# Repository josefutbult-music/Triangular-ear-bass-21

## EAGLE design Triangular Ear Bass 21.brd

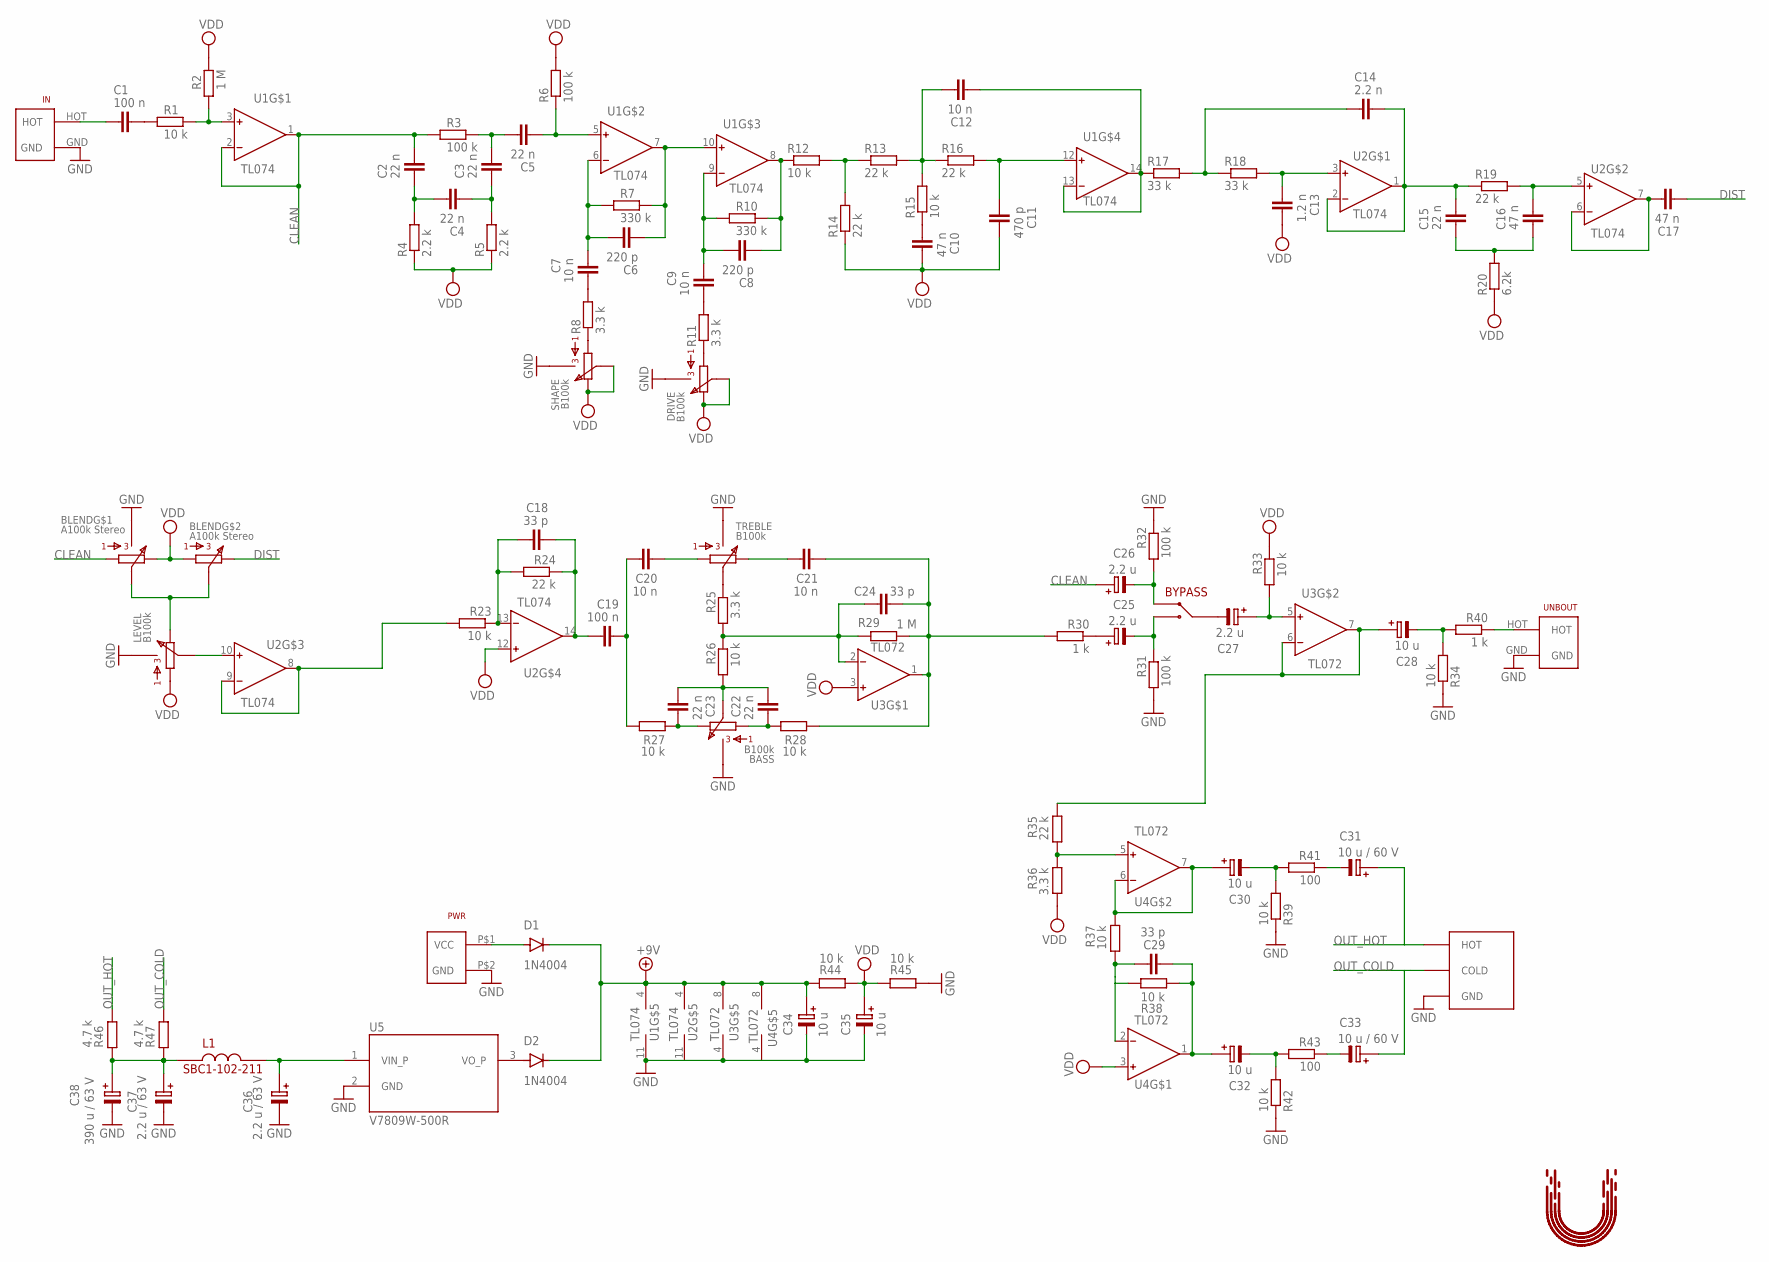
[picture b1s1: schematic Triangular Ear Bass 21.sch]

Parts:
BALOUT: HOT_COLD
BASS: B100k; RK09L1140
BLEND: A100k Stereo; RK09L124000Z
BYPASS: BUTTON; 3-HOLES
C1, C19: 100 n; C050-035X075
C2, C3, C4, C5, C15, C22, C23: 22 n; C050-035X075
C6, C8: 220 p; C050-035X075
C7, C9, C12, C20, C21: 10 n; C050-035X075
C10, C16, C17: 47 n; C050-035X075
C11: 470 p; C050-035X075
C13: 1.2 n; C050-035X075
C14: 2.2 n; C050-035X075
C18, C24, C29: 33 p; C050-035X075
C25, C26, C27: 2.2 u; E2,0-5
C28, C30, C32, C34, C35: 10 u; E2,0-5
C31, C33: 10 u / 60 V; E2,0-5
C36, C37: 2.2 u / 63 V; E2,0-5
C38: 390 u / 63 V; E5,0-12,5
D1, D2: 1N4004; DO41-10
DRIVE: B100k; RK09L1140
IN: UNBALANCED_INPUT_JACK; BALANCED_INPUT_JACK
L1: SBC1-102-211
LEVEL: B100k; RK09L1140
PWR: PWR
R1, R12, R15, R23, R26, R27, R28, R33, R34, R37, R38, R39, R42, R44, R45: 10 k; 0204/7
R2, R29: 1 M; 0204/7
R3, R6, R31, R32: 100 k; 0204/7
R4, R5: 2.2 k; 0204/7
R7, R10: 330 k; 0204/7
R8, R11, R25, R36: 3.3 k; 0204/7
R13, R14, R16, R19, R24, R35: 22 k; 0204/7
R17, R18: 33 k; 0204/7
R20: 6.2k; 0204/7
R30, R40: 1 k; 0204/7
R41, R43: 100; 0204/7
R46, R47: 4.7 k; 0204/7
SHAPE: B100k; RK09L1140
TREBLE: B100k; RK09L1140
U1, U2: TL074; DIP762W53P254L1969H508Q14B
U3, U4: TL072; DIP762W53P254L980H508Q8B
U5: V7809W-500R; CONV_V7809W-500R
U$1: UTBULT_DESIGN4; UD_4
UNBOUT: UNBALANCED_INPUT_JACK; BALANCED_INPUT_JACK

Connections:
48V: C37.+, C38.+, L1.P$1, R46.1, R47.1
+9V: C34.+, D1.C, D2.C, R44.1, U1.4 (V+), U2.4 (V+), U3.8 (V+), U4.8 (V+)
BLEND_OUT: R23.2, U2.8 (OUT), U2.9 (IN-)
CLEAN: BLEND.P$1 (1), C2.2, C26.+, R3.1, U1.1 (OUT), U1.2 (IN-)
DIST: BLEND.P$8 (3), C17.1
GND: BALOUT.P$1 (GND), BASS.P$4, BASS.P$5, BLEND.P$4, BLEND.P$5, C34.-, C35.-, C36.-, C37.-, C38.-, DRIVE.P$4, DRIVE.P$5, IN.GND, LEVEL.P$4, LEVEL.P$5, PWR.P$2 (GND), R31.2, R32.1, R34.1, R39.1, R42.1, R45.2, SHAPE.P$4, SHAPE.P$5, TREBLE.P$4, TREBLE.P$5, U1.11 (V-), U2.11 (V-), U3.4 (V-), U4.4 (V-), U5.2 (GND), UNBOUT.GND
unnamed: C1.1, IN.HOT
unnamed: C1.2, R1.1
unnamed: R1.2, R2.1, U1.3 (IN+)
unnamed: BLEND.P$2 (2), BLEND.P$7 (2), LEVEL.P$3 (3)
unnamed: C2.1, C4.2, R4.2
unnamed: C3.1, C4.1, R5.2
unnamed: C3.2, C5.2, R3.2
unnamed: C5.1, R6.1, U1.5 (IN+)
unnamed: C6.2, C7.1, R7.1, U1.6 (IN-)
unnamed: C6.1, R7.2, U1.7 (OUT), U1.10 (IN+)
unnamed: C7.2, R8.2
unnamed: R8.1, SHAPE.P$1 (1)
unnamed: C8.2, C9.1, R10.1, U1.9 (IN-)
unnamed: C8.1, R10.2, R12.1, U1.8 (OUT)
unnamed: C9.2, R11.2
unnamed: DRIVE.P$1 (1), R11.1
unnamed: C10.1, R15.1
unnamed: R12.2, R13.1, R14.2
unnamed: C12.2, R13.2, R15.2, R16.1
unnamed: C11.1, R16.2, U1.12 (IN+)
unnamed: C14.1, R17.2, R18.1
unnamed: C12.1, R17.1, U1.13 (IN-), U1.14 (OUT)
unnamed: C13.1, R18.2, U2.3 (IN+)
unnamed: C14.2, C15.2, R19.1, U2.1 (OUT), U2.2 (IN-)
unnamed: C16.2, R19.2, U2.5 (IN+)
unnamed: C15.1, C16.1, R20.2
unnamed: C17.2, U2.6 (IN-), U2.7 (OUT)
unnamed: LEVEL.P$2 (2), U2.10 (IN+)
unnamed: C18.2, R23.1, R24.2, U2.13 (IN-)
unnamed: C18.1, C19.2, R24.1, U2.14 (OUT)
unnamed: C20.1, TREBLE.P$1 (1)
unnamed: C21.2, TREBLE.P$3 (3)
unnamed: C19.1, C20.2, R27.2
unnamed: R25.1, TREBLE.P$2 (2)
unnamed: C24.2, R25.2, R26.1, R29.1, U3.2 (IN-)
unnamed: BASS.P$3 (3), C23.2, R27.1
unnamed: BASS.P$2 (2), C22.1, C23.1, R26.2
unnamed: BASS.P$1 (1), C22.2, R28.2
unnamed: C25.+, R30.1
unnamed: C21.1, C24.1, R28.1, R29.2, R30.2, U3.1 (OUT)
unnamed: BYPASS.P$3, C25.-, R31.1
unnamed: BYPASS.P$1, C26.-, R32.2
unnamed: BYPASS.P$2, C27.-
unnamed: C27.+, R33.2, U3.5 (IN+)
unnamed: C28.+, R35.1, U3.6 (IN-), U3.7 (OUT)
unnamed: C28.-, R34.2, R40.2
unnamed: R35.2, R36.1, U4.5 (IN+)
unnamed: C29.2, R37.2, R38.1, U4.2 (IN-)
unnamed: C30.+, R37.1, U4.6 (IN-), U4.7 (OUT)
unnamed: C30.-, R39.2, R41.2
unnamed: R40.1, UNBOUT.HOT
unnamed: C31.-, R41.1
unnamed: C29.1, C32.+, R38.2, U4.1 (OUT)
unnamed: C32.-, R42.2, R43.2
unnamed: C33.-, R43.1
unnamed: D1.A, PWR.P$1 (VCC)
unnamed: D2.A, U5.3 (VO_P)
unnamed: C36.+, L1.P$2, U5.1 (VIN_P)
OUT_COLD: BALOUT.P$3 (COLD), C33.+, R47.2
OUT_HOT: BALOUT.P$2 (HOT), C31.+, R46.2
VDD: BLEND.P$3 (3), BLEND.P$6 (1), C10.2, C11.2, C13.2, C35.+, DRIVE.P$2 (2), DRIVE.P$3 (3), LEVEL.P$1 (1), R2.2, R4.1, R5.1, R6.2, R14.1, R20.1, R33.1, R36.2, R44.2, R45.1, SHAPE.P$2 (2), SHAPE.P$3 (3), U2.12 (IN+), U3.3 (IN+), U4.3 (IN+)

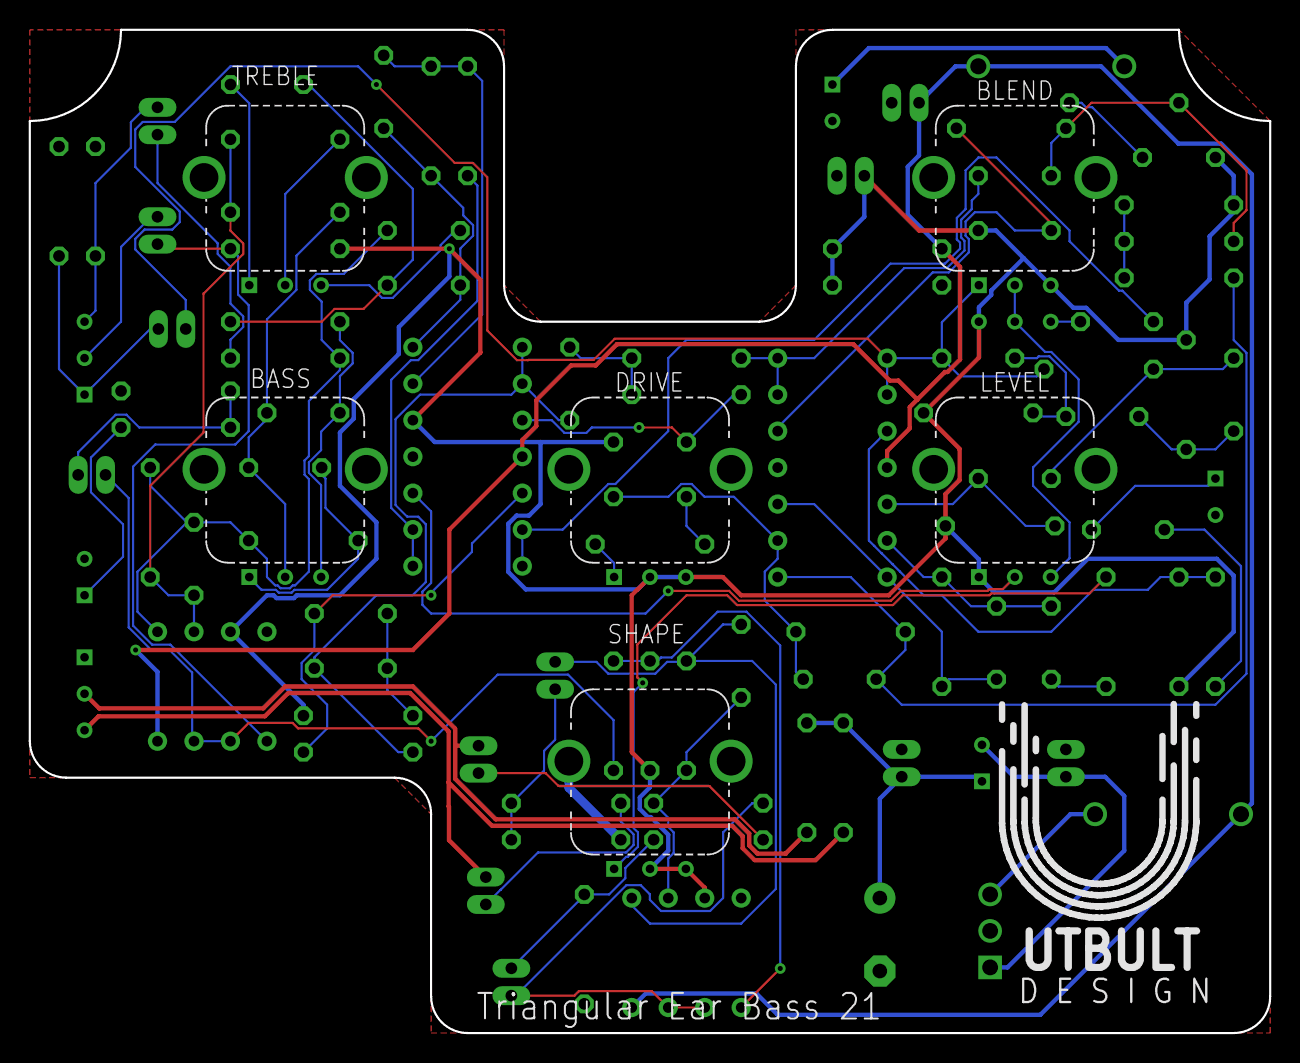
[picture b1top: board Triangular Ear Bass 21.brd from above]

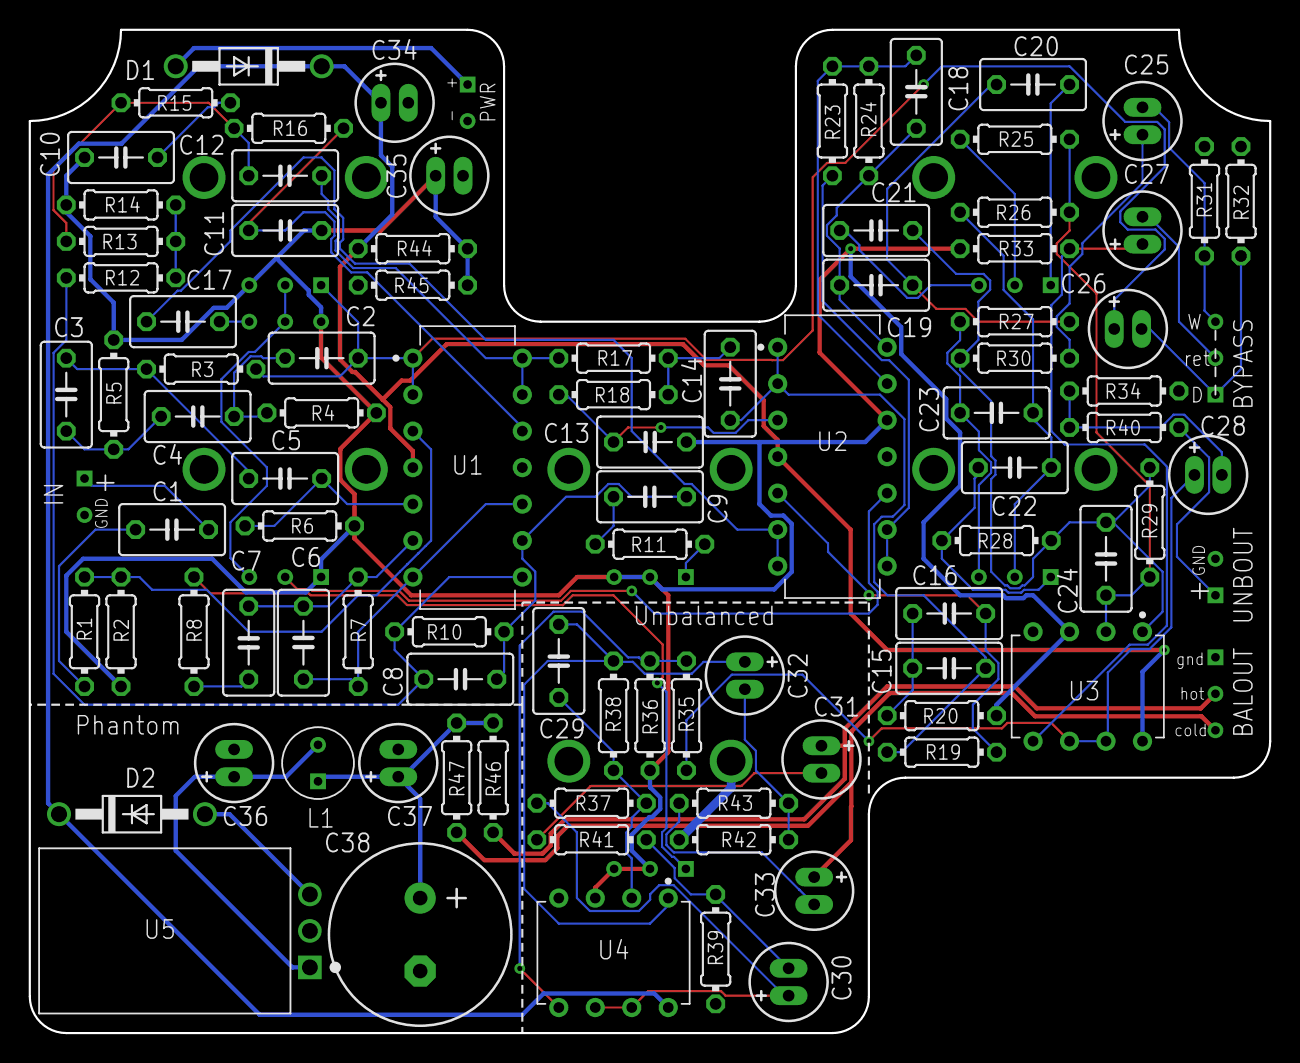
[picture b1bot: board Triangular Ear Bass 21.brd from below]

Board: 2 copper layers, 86.4 x 69.8 mm, 102 parts (95 on the bottom side), 67 nets.

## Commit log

2020-12-26 Fixed spacing for capacitors
2021-02-09 Add gerber file
